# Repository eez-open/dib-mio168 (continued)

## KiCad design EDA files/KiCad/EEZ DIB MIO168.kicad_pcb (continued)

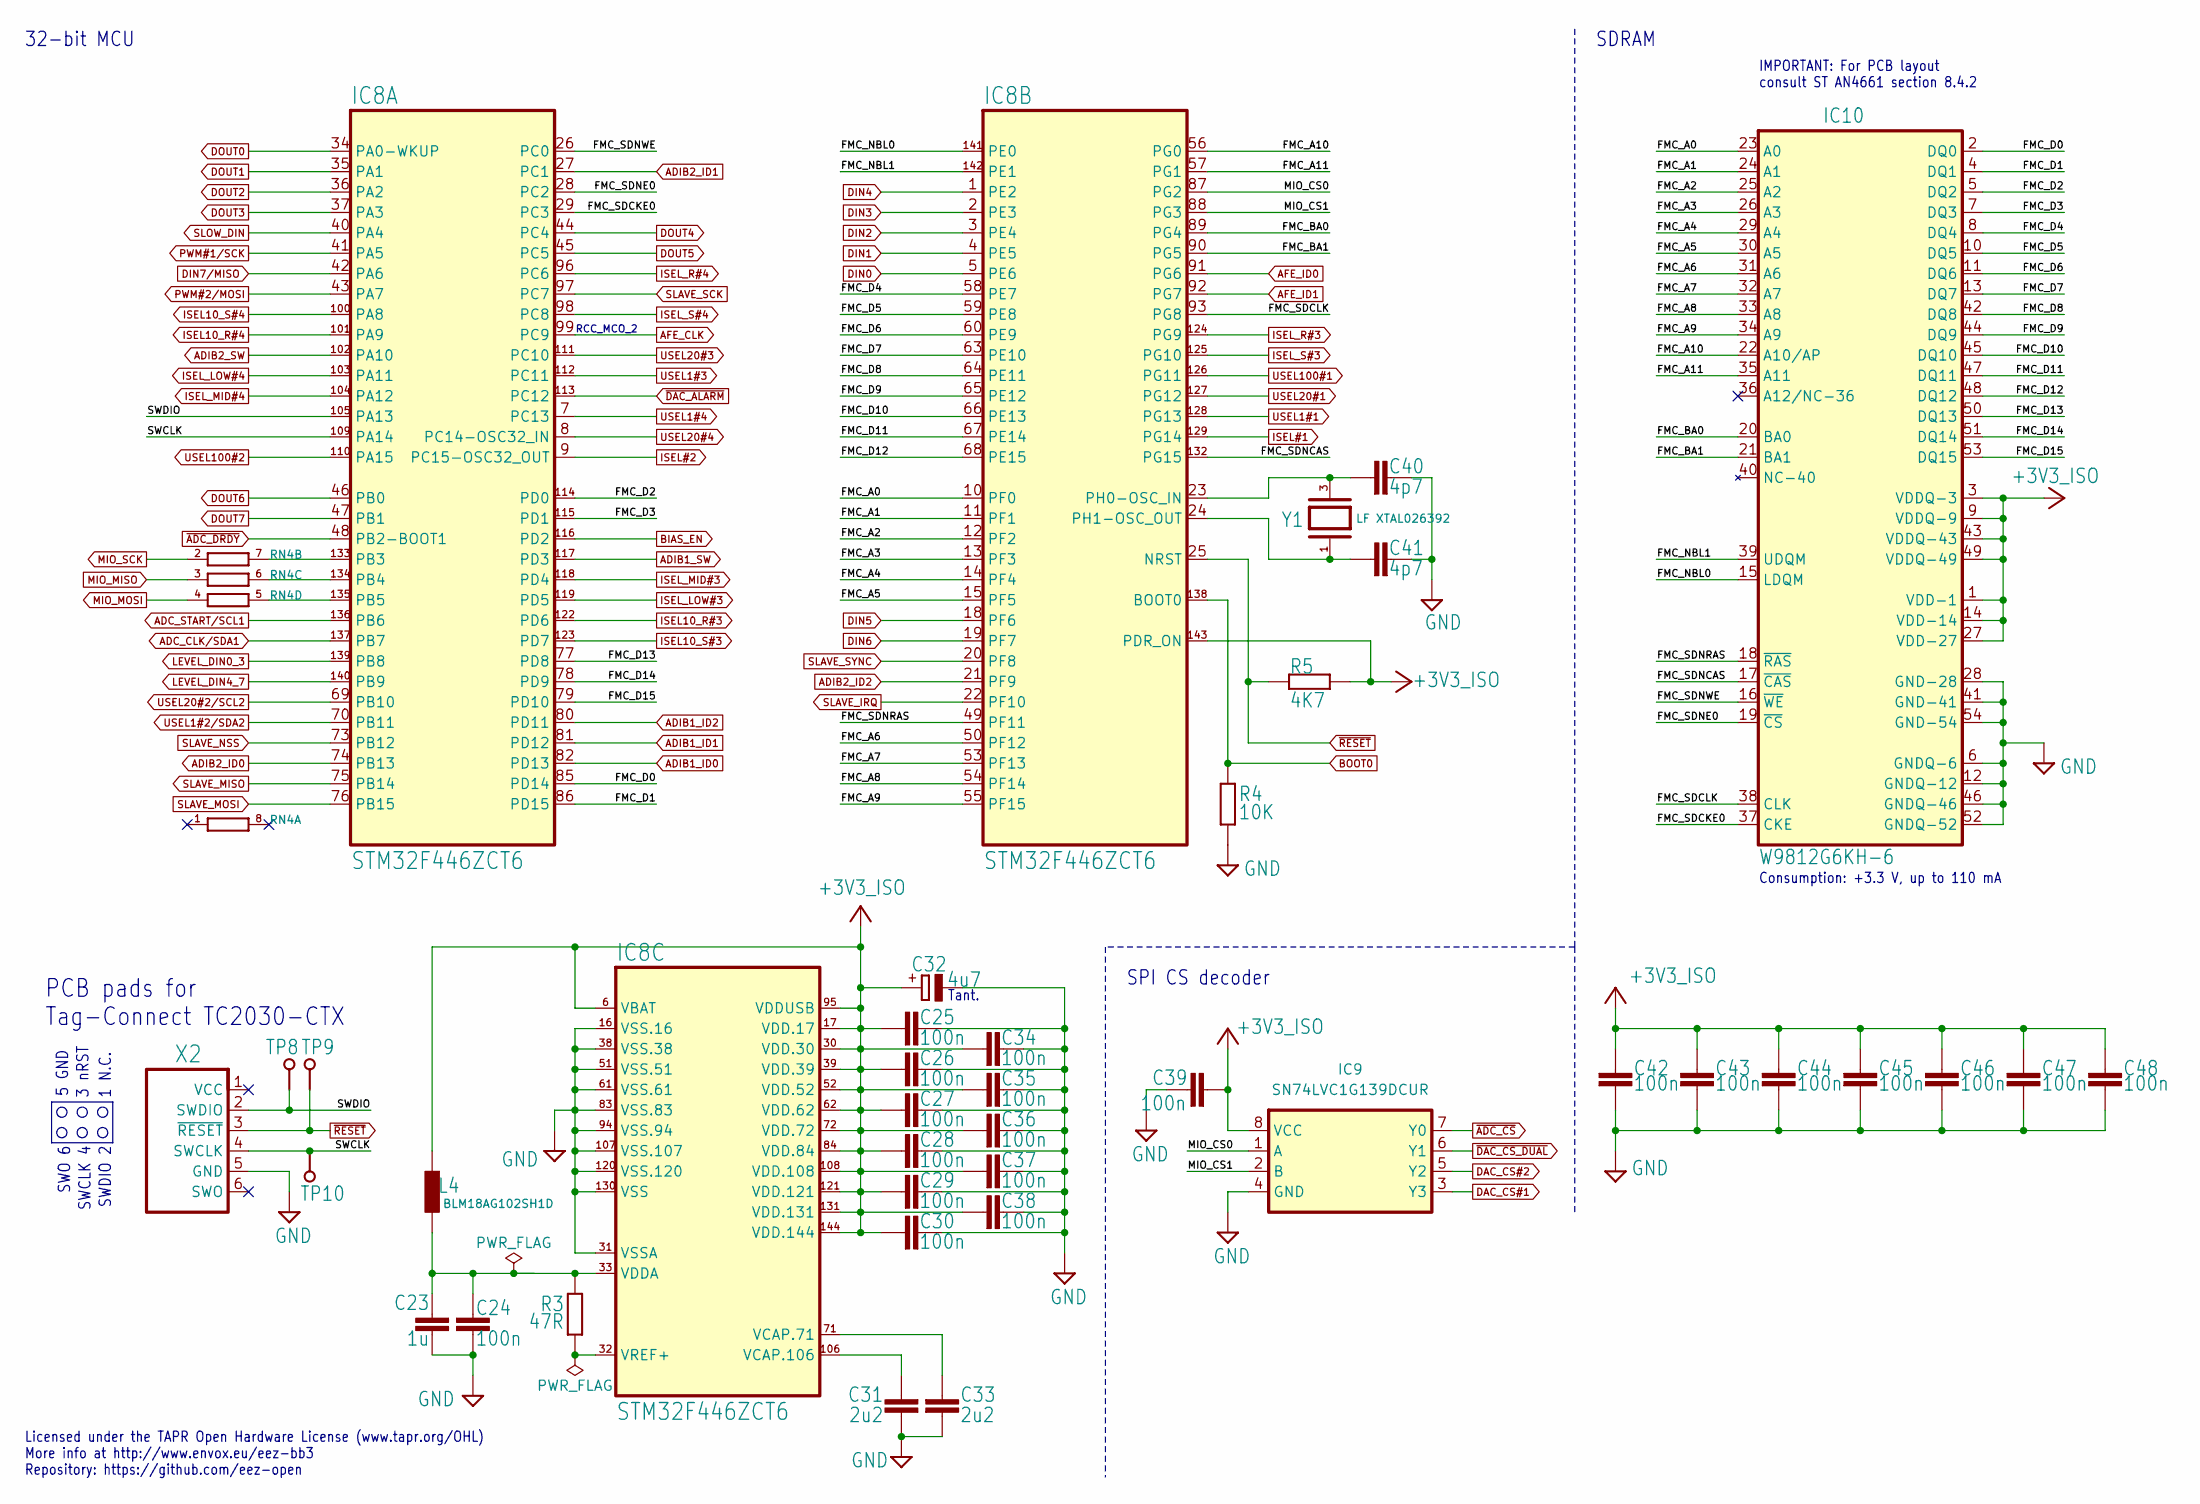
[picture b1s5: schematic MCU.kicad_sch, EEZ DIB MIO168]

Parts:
C23: 1u; C_0805_2012Metric; DigiKey 490-10494-2-ND
C24, C25, C26, C27, C28, C29, C30, C34, C35, C36, C37, C38, C39, C42, C43, C44, C45, C46, C47, C48: 100n; C_0603_1608Metric; DigiKey 1276-1005-2-ND
C31, C33: 2u2; C_0805_2012Metric; DigiKey 1276-2954-1-ND
C32: 4u7; EC1206; DigiKey 399-9717-1-ND
C40, C41: 4p7; C_0603_1608Metric; DigiKey 311-1740-1-ND
IC8: STM32F446ZCT6; LQFP-144_20X20MM; DigiKey 497-17473-ND
IC9: SN74LVC1G139DCUR; DCU8; DigiKey 296-18203-2-ND
IC10: W9812G6KH-6; TSOPII-54; DigiKey W9812G6KH-6-ND
L4: BLM18AG102SH1D; BEAD0603; DigiKey 490-7809-1-ND
R3: 47R; R_0805_2012Metric; DigiKey P47.0CCT-ND
R4: 10K; R_0805_2012Metric; DigiKey CRGH0603F10K
R5: 4K7; R_0805_2012Metric; DigiKey 311-4.70KCRCT-ND
RN4: DR1206-33R-4/8; CAY16; DigiKey CAY16-330J4LFCT-ND
TP8, TP9, TP10: PCB_TEST_TABSHIELD; Testhole 24_50mils
X2: TC2030
Y1: LF XTAL026392; 12SMX(B); DigiKey 1923-1009-ND

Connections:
+3V3_ISO: C25.1, C26.1, C27.1, C28.1, C29.1, C30.1, C32.+, C34.1, C35.1, C36.1, C37.1, C38.1, C39.1, C42.1, C43.1, C44.1, C45.1, C46.1, C47.1, C48.1, IC8.6 (VBAT), IC8.17 (VDD.17), IC8.30 (VDD.30), IC8.39 (VDD.39), IC8.52 (VDD.52), IC8.62 (VDD.62), IC8.72 (VDD.72), IC8.84 (VDD.84), IC8.95 (VDDUSB), IC8.108 (VDD.108), IC8.121 (VDD.121), IC8.131 (VDD.131), IC8.143 (PDR_ON), IC8.144 (VDD.144), IC9.8 (VCC), IC10.1 (VDD-1), IC10.3 (VDDQ-3), IC10.9 (VDDQ-9), IC10.14 (VDD-14), IC10.27 (VDD-27), IC10.43 (VDDQ-43), IC10.49 (VDDQ-49), L4.1, R5.1; also elsewhere on the board
/MCU/FMC_A0: IC8.10 (PF0), IC10.23 (A0)
/MCU/FMC_A1: IC8.11 (PF1), IC10.24 (A1)
/MCU/FMC_A2: IC8.12 (PF2), IC10.25 (A2)
/MCU/FMC_A3: IC8.13 (PF3), IC10.26 (A3)
/MCU/FMC_A4: IC8.14 (PF4), IC10.29 (A4)
/MCU/FMC_A5: IC8.15 (PF5), IC10.30 (A5)
/MCU/FMC_A6: IC8.50 (PF12), IC10.31 (A6)
/MCU/FMC_A7: IC8.53 (PF13), IC10.32 (A7)
/MCU/FMC_A8: IC8.54 (PF14), IC10.33 (A8)
/MCU/FMC_A9: IC8.55 (PF15), IC10.34 (A9)
/MCU/FMC_A10: IC8.56 (PG0), IC10.22 (A10/AP)
/MCU/FMC_A11: IC8.57 (PG1), IC10.35 (A11)
/MCU/FMC_BA0: IC8.89 (PG4), IC10.20 (BA0)
/MCU/FMC_BA1: IC8.90 (PG5), IC10.21 (BA1)
/MCU/FMC_D0: IC8.85 (PD14), IC10.2 (DQ0)
/MCU/FMC_D1: IC8.86 (PD15), IC10.4 (DQ1)
/MCU/FMC_D2: IC8.114 (PD0), IC10.5 (DQ2)
/MCU/FMC_D3: IC8.115 (PD1), IC10.7 (DQ3)
/MCU/FMC_D4: IC8.58 (PE7), IC10.8 (DQ4)
/MCU/FMC_D5: IC8.59 (PE8), IC10.10 (DQ5)
/MCU/FMC_D6: IC8.60 (PE9), IC10.11 (DQ6)
/MCU/FMC_D7: IC8.63 (PE10), IC10.13 (DQ7)
/MCU/FMC_D8: IC8.64 (PE11), IC10.42 (DQ8)
/MCU/FMC_D9: IC8.65 (PE12), IC10.44 (DQ9)
/MCU/FMC_D10: IC8.66 (PE13), IC10.45 (DQ10)
/MCU/FMC_D11: IC8.67 (PE14), IC10.47 (DQ11)
/MCU/FMC_D12: IC8.68 (PE15), IC10.48 (DQ12)
/MCU/FMC_D13: IC8.77 (PD8), IC10.50 (DQ13)
/MCU/FMC_D14: IC8.78 (PD9), IC10.51 (DQ14)
/MCU/FMC_D15: IC8.79 (PD10), IC10.53 (DQ15)
/MCU/FMC_NBL0: IC8.141 (PE0), IC10.15 (LDQM)
/MCU/FMC_NBL1: IC8.142 (PE1), IC10.39 (UDQM)
/MCU/FMC_SDCKE0: IC8.29 (PC3), IC10.37 (CKE)
/MCU/FMC_SDCLK: IC8.93 (PG8), IC10.38 (CLK)
/MCU/FMC_SDNCAS: IC8.132 (PG15), IC10.17 (~CAS)
/MCU/FMC_SDNE0: IC8.28 (PC2), IC10.19 (~CS)
/MCU/FMC_SDNRAS: IC8.49 (PF11), IC10.18 (~RAS)
/MCU/FMC_SDNWE: IC8.26 (PC0), IC10.16 (~WE)
/MCU/MIO_CS0: IC8.87 (PG2), IC9.1 (A)
/MCU/MIO_CS1: IC8.88 (PG3), IC9.2 (B)
/MCU/SWCLK: IC8.109 (PA14), TP10.1, X2.4 (SWCLK)
/MCU/SWDIO: IC8.105 (PA13), TP8.1, X2.2 (SWDIO)
ADC_CLK/SDA1: IC8.137 (PB7); also elsewhere on the board
ADC_START/SCL1: IC8.136 (PB6); also elsewhere on the board
ADIB1_ID0: IC8.82 (PD13); also elsewhere on the board
ADIB1_ID1: IC8.81 (PD12); also elsewhere on the board
ADIB1_ID2: IC8.80 (PD11); also elsewhere on the board
ADIB1_SW: IC8.117 (PD3); also elsewhere on the board
ADIB2_ID0: IC8.74 (PB13); also elsewhere on the board
ADIB2_ID1: IC8.27 (PC1); also elsewhere on the board
ADIB2_ID2: IC8.21 (PF9); also elsewhere on the board
ADIB2_SW: IC8.102 (PA10); also elsewhere on the board
AFE_CLK: IC8.99 (PC9); also elsewhere on the board
AFE_ID0: IC8.91 (PG6); also elsewhere on the board
AFE_ID1: IC8.92 (PG7); also elsewhere on the board
BIAS_EN: IC8.116 (PD2); also elsewhere on the board
BOOT0: IC8.138 (BOOT0), R4.2; also elsewhere on the board
DAC_CS#1: IC9.3 (Y3); also elsewhere on the board
DAC_CS#2: IC9.5 (Y2); also elsewhere on the board
DIN0: IC8.5 (PE6); also elsewhere on the board
DIN1: IC8.4 (PE5); also elsewhere on the board
DIN2: IC8.3 (PE4); also elsewhere on the board
DIN3: IC8.2 (PE3); also elsewhere on the board
DIN4: IC8.1 (PE2); also elsewhere on the board
DIN5: IC8.18 (PF6); also elsewhere on the board
DIN6: IC8.19 (PF7); also elsewhere on the board
DIN7/MISO: IC8.42 (PA6); also elsewhere on the board
DOUT0: IC8.34 (PA0-WKUP); also elsewhere on the board
DOUT1: IC8.35 (PA1); also elsewhere on the board
DOUT2: IC8.36 (PA2); also elsewhere on the board
DOUT3: IC8.37 (PA3); also elsewhere on the board
DOUT4: IC8.44 (PC4); also elsewhere on the board
DOUT5: IC8.45 (PC5); also elsewhere on the board
DOUT6: IC8.46 (PB0); also elsewhere on the board
DOUT7: IC8.47 (PB1); also elsewhere on the board
GND: C23.2, C24.2, C25.2, C26.2, C27.2, C28.2, C29.2, C30.2, C31.1, C32.-, C33.1, C34.2, C35.2, C36.2, C37.2, C38.2, C39.2, C40.1, C41.1, C42.2, C43.2, C44.2, C45.2, C46.2, C47.2, C48.2, IC8.16 (VSS.16), IC8.31 (VSSA), IC8.38 (VSS.38), IC8.51 (VSS.51), IC8.61 (VSS.61), IC8.83 (VSS.83), IC8.94 (VSS.94), IC8.107 (VSS.107), IC8.120 (VSS.120), IC8.130 (VSS), IC9.4 (GND), IC10.6 (GNDQ-6), IC10.12 (GNDQ-12), IC10.28 (GND-28), IC10.41 (GND-41), IC10.46 (GNDQ-46), IC10.52 (GNDQ-52), IC10.54 (GND-54), R4.1, X2.5 (GND); also elsewhere on the board
ISEL10_R#3: IC8.122 (PD6); also elsewhere on the board
ISEL10_R#4: IC8.101 (PA9); also elsewhere on the board
ISEL10_S#3: IC8.123 (PD7); also elsewhere on the board
ISEL10_S#4: IC8.100 (PA8); also elsewhere on the board
ISEL#1: IC8.129 (PG14); also elsewhere on the board
ISEL#2: IC8.9 (PC15-OSC32_OUT); also elsewhere on the board
ISEL_LOW#3: IC8.119 (PD5); also elsewhere on the board
ISEL_LOW#4: IC8.103 (PA11); also elsewhere on the board
ISEL_MID#3: IC8.118 (PD4); also elsewhere on the board
ISEL_MID#4: IC8.104 (PA12); also elsewhere on the board
ISEL_R#3: IC8.124 (PG9); also elsewhere on the board
ISEL_R#4: IC8.96 (PC6); also elsewhere on the board
ISEL_S#3: IC8.125 (PG10); also elsewhere on the board
ISEL_S#4: IC8.98 (PC8); also elsewhere on the board
LEVEL_DIN0_3: IC8.139 (PB8); also elsewhere on the board
LEVEL_DIN4_7: IC8.140 (PB9); also elsewhere on the board
MIO_MISO: RN4.3 (1); also elsewhere on the board
MIO_MOSI: RN4.4 (1); also elsewhere on the board
MIO_SCK: RN4.2 (1); also elsewhere on the board
unnamed: IC8.133 (PB3), RN4.7 (2)
unnamed: IC8.134 (PB4), RN4.6 (2)
unnamed: IC8.135 (PB5), RN4.5 (2)
unnamed: C40.2, IC8.23 (PH0-OSC_IN), Y1.3, Y1.4 (NC)
unnamed: C41.2, IC8.24 (PH1-OSC_OUT), Y1.1, Y1.2 (NC)
unnamed: C33.2, IC8.71 (VCAP.71)
unnamed: C31.2, IC8.106 (VCAP.106)
unnamed: C23.1, C24.1, IC8.33 (VDDA), L4.2, R3.1
unnamed: IC8.32 (VREF+), R3.2
PWM#1/SCK: IC8.41 (PA5); also elsewhere on the board
PWM#2/MOSI: IC8.43 (PA7); also elsewhere on the board
SLAVE_IRQ: IC8.22 (PF10); also elsewhere on the board
SLAVE_MISO: IC8.75 (PB14); also elsewhere on the board
SLAVE_MOSI: IC8.76 (PB15); also elsewhere on the board
SLAVE_NSS: IC8.73 (PB12); also elsewhere on the board
SLAVE_SCK: IC8.97 (PC7); also elsewhere on the board
SLAVE_SYNC: IC8.20 (PF8); also elsewhere on the board
SLOW_DIN: IC8.40 (PA4); also elsewhere on the board
USEL1#1: IC8.128 (PG13); also elsewhere on the board
USEL1#2/SDA2: IC8.70 (PB11); also elsewhere on the board
USEL1#3: IC8.112 (PC11); also elsewhere on the board
USEL1#4: IC8.7 (PC13); also elsewhere on the board
USEL20#1: IC8.127 (PG12); also elsewhere on the board
USEL20#2/SCL2: IC8.69 (PB10); also elsewhere on the board
USEL20#3: IC8.111 (PC10); also elsewhere on the board
USEL20#4: IC8.8 (PC14-OSC32_IN); also elsewhere on the board
USEL100#1: IC8.126 (PG11); also elsewhere on the board
USEL100#2: IC8.110 (PA15); also elsewhere on the board
~ADC_CS: IC9.7 (Y0); also elsewhere on the board
~ADC_DRDY: IC8.48 (PB2-BOOT1); also elsewhere on the board
~DAC_ALARM: IC8.113 (PC12); also elsewhere on the board
~DAC_CS_DUAL: IC9.6 (Y1); also elsewhere on the board
~RESET: IC8.25 (NRST), R5.2, TP9.1, X2.3 (~RESET); also elsewhere on the board

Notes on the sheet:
3 nRST
SWO 6
32-bit MCU
SWCLK 4
SWDIO 2
1 N.C.
Tant.
RCC_MCO_2
5 GND
PCB pads for Tag-Connect TC2030-CTX
Consumption: +3.3 V, up to 110 mA
SPI CS decoder
SDRAM
IMPORTANT: For PCB layout consult ST AN4661 section 8.4.2
Licensed under the TAPR Open Hardware License (www.tapr.org/OHL) More info at http://www.envox.eu/eez-bb3 Repository: https://github.com/eez-open

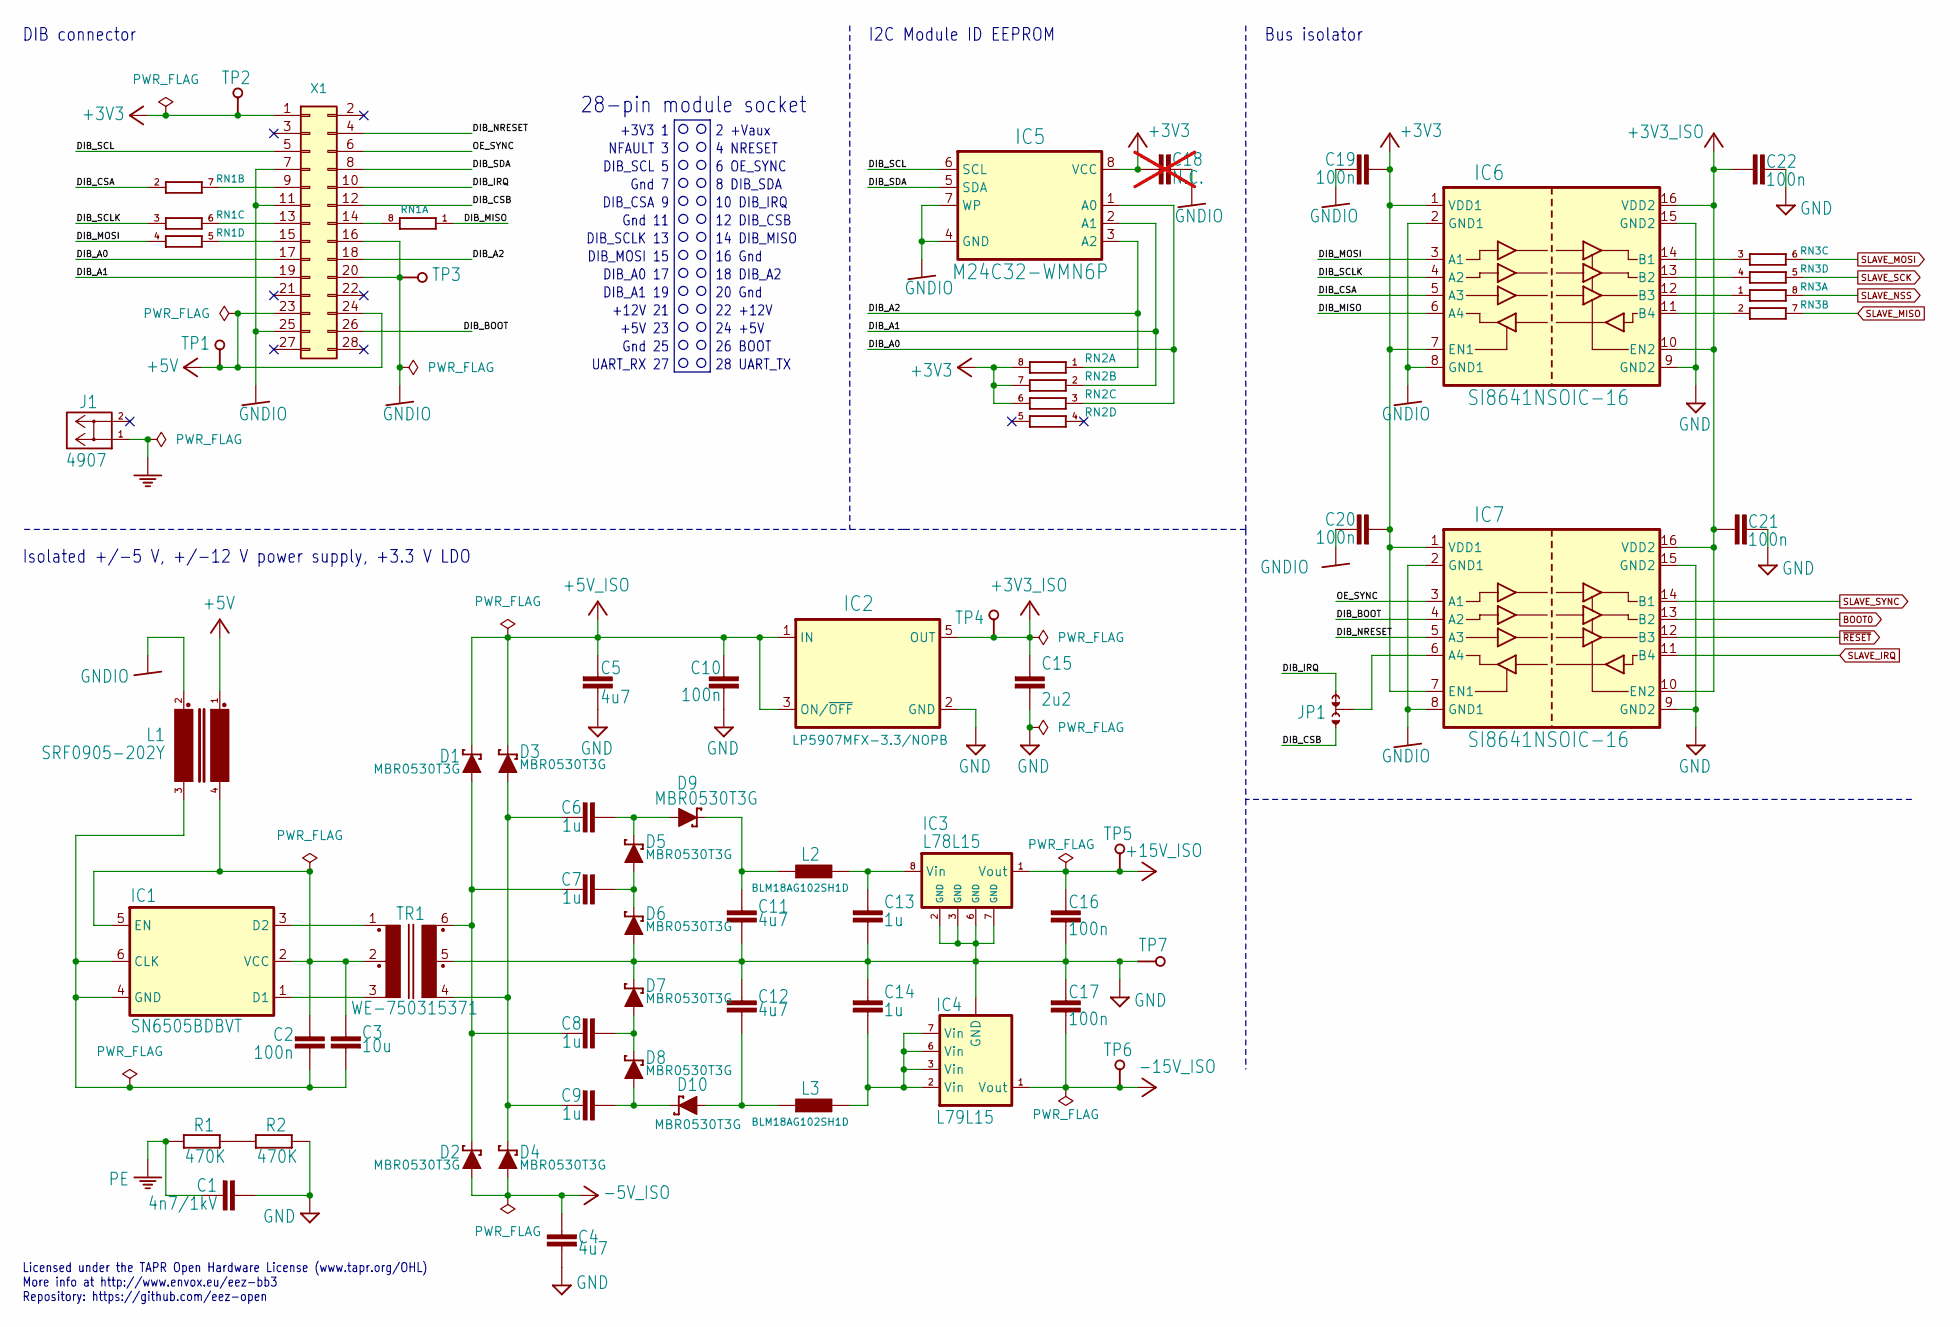
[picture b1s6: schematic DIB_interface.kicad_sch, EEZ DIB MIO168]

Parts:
C1: 4n7/1kV; C_1206_3216Metric; DigiKey 732-12074-2-ND
C2, C10, C16, C17, C19, C20, C21, C22: 100n; C_0603_1608Metric; DigiKey 1276-1005-2-ND
C3: 10u; C_1206_3216Metric; DigiKey 1276-2872-1-ND
C4, C5, C11, C12: 4u7; C_0805_2012Metric; DigiKey 490-14466-1-ND
C6, C7, C8, C9, C13, C14: 1u; C_0805_2012Metric; DigiKey 490-10494-2-ND
C15: 2u2; C_0805_2012Metric; DigiKey 1276-2954-1-ND
C18: N.C.; C_0603_1608Metric; not fitted
D1, D2, D3, D4, D5, D6, D7, D8, D9, D10: MBR0530T3G; SOD123; DigiKey 863-MBR0530T3G
IC1: SN6505BDBVT; DBV0006A_N; DigiKey 296-43154-2-ND
IC2: LP5907MFX-3.3/NOPB; SOT23-5L_STM; DigiKey 296-38557-2-ND
IC3: L78L15; SOIC127P600X173-8N; DigiKey MC78L15ACDR2GOSDKR-ND
IC4: L79L15; SOIC127P600X173-8N; DigiKey MC79L15ABDR2GOSDKR
IC5: M24C32-WMN6P; SOIC127P600X173-8N; DigiKey 497-8572-5-ND
IC6, IC7: SI8641NSOIC-16; SOIC127P600X265-16N; DigiKey 336-2566-ND
J1: 4907; DigiKey 36-4907-ND
JP1: JP3-CUT-0805-ROTATED; JP3 shorted
L1: SRF0905-202Y; SRF0905; DigiKey SRF0905-202YCT-ND
L2, L3: BLM18AG102SH1D; BEAD0603; DigiKey 490-7809-1-ND
R1, R2: 470K; R_0805_2012Metric; DigiKey 13-RT0805FRE07470KLDKR-ND
RN1, RN3: DR1206-33R-4/8; CAY16; DigiKey CAY16-330J4LFCT-ND
RN2: DR1206-47K-4/8; CAY16; DigiKey CAY16-330J4LFCT-ND
TP1, TP2, TP3, TP4, TP5, TP6, TP7: PCB_TEST_TABSHIELD; Testhole 24_50mils
TR1: WE-750315371; MURATA_78615; DigiKey 1297-1178-1-ND
X1: 77317-104-28LF; DigiKey S2111EC-14-ND

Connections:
+3V3: C18.2, C19.1, C20.1, IC5.8 (VCC), IC6.1 (VDD1), IC6.7 (EN1), IC7.1 (VDD1), IC7.7 (EN1), RN2.6 (2), RN2.7 (2), RN2.8 (2), TP2.1, X1.1
+3V3_ISO: C15.1, C21.2, C22.2, IC2.5 (OUT), IC6.10 (EN2), IC6.16 (VDD2), IC7.10 (EN2), IC7.16 (VDD2), TP4.1; also elsewhere on the board
+5V: L1.1, TP1.1, X1.23, X1.24
+5V_ISO: C5.2, C10.1, D1.C, D3.C, IC2.1 (IN), IC2.3 (ON/~OFF); also elsewhere on the board
+15V_ISO: C16.1, IC3.1 (Vout), TP5.1; also elsewhere on the board
-5V_ISO: C4.2, D2.A, D4.A; also elsewhere on the board
-15V_ISO: C17.2, IC4.1 (Vout), TP6.1; also elsewhere on the board
/DIB interface/DIB_A0: IC5.1 (A0), RN2.3 (1), X1.17
/DIB interface/DIB_A1: IC5.2 (A1), RN2.2 (1), X1.19
/DIB interface/DIB_A2: IC5.3 (A2), RN2.1, X1.18
/DIB interface/DIB_BOOT: IC7.4 (A2), X1.26
/DIB interface/DIB_CSA: IC6.5 (A3), RN1.2 (1)
/DIB interface/DIB_CSB: JP1.NO, X1.12
/DIB interface/DIB_IRQ: JP1.NC, X1.10
/DIB interface/DIB_MISO: IC6.6 (A4), RN1.1
/DIB interface/DIB_MOSI: IC6.3 (A1), RN1.4 (1)
/DIB interface/DIB_NRESET: IC7.5 (A3), X1.4
/DIB interface/DIB_SCL: IC5.6 (SCL), X1.5
/DIB interface/DIB_SCLK: IC6.4 (A2), RN1.3 (1)
/DIB interface/DIB_SDA: IC5.5 (SDA), X1.8
/DIB interface/OE_SYNC: IC7.3 (A1), X1.6
BOOT0: IC7.13 (B2); also elsewhere on the board
GND: C1.2, C4.1, C5.1, C10.2, C11.2, C12.1, C13.1, C14.2, C15.2, C16.2, C17.1, C21.1, C22.1, D6.A, D7.C, IC2.2 (GND), IC3.2 (GND), IC3.3 (GND), IC3.6 (GND), IC3.7 (GND), IC4.5 (GND), IC6.9 (GND2), IC6.15 (GND2), IC7.9 (GND2), IC7.15 (GND2), R2.2, TP7.1, TR1.5; also elsewhere on the board
GNDIO: C18.1, C19.2, C20.2, IC5.4 (GND), IC5.7 (WP), IC6.2 (GND1), IC6.8 (GND1), IC7.2 (GND1), IC7.8 (GND1), L1.2, TP3.1, X1.7, X1.11, X1.16, X1.20, X1.25
unnamed: C6.1, D5.C, D9.A
unnamed: C6.2, C9.2, D3.A, D4.C, TR1.4
unnamed: C7.1, D5.A, D6.C
unnamed: C7.2, C8.2, D1.A, D2.C, TR1.6
unnamed: C8.1, D7.A, D8.C
unnamed: C9.1, D8.A, D10.C
unnamed: C11.1, D9.C, L2.1
unnamed: C12.2, D10.A, L3.1
unnamed: C14.1, IC4.2 (Vin), IC4.3 (Vin), IC4.6 (Vin), IC4.7 (Vin), L3.2
unnamed: C2.2, C3.1, IC1.4 (GND), IC1.6 (CLK), L1.3
unnamed: IC1.1 (D1), TR1.3
unnamed: IC1.3 (D2), TR1.1
unnamed: C2.1, C3.2, IC1.2 (VCC), IC1.5 (EN), L1.4, TR1.2
unnamed: C13.2, IC3.8 (Vin), L2.2
unnamed: IC6.14 (B1), RN3.3 (1)
unnamed: IC6.13 (B2), RN3.4 (1)
unnamed: IC6.12 (B3), RN3.1
unnamed: IC6.11 (B4), RN3.2 (1)
unnamed: IC7.6 (A4), JP1.COM
unnamed: R1.2, R2.1
unnamed: RN1.8 (2), X1.14
unnamed: RN1.7 (2), X1.9
unnamed: RN1.6 (2), X1.13
unnamed: RN1.5 (2), X1.15
PE: C1.1, J1.1, R1.1
SLAVE_IRQ: IC7.11 (B4); also elsewhere on the board
SLAVE_MISO: RN3.7 (2); also elsewhere on the board
SLAVE_MOSI: RN3.6 (2); also elsewhere on the board
SLAVE_NSS: RN3.8 (2); also elsewhere on the board
SLAVE_SCK: RN3.5 (2); also elsewhere on the board
SLAVE_SYNC: IC7.14 (B1); also elsewhere on the board
~RESET: IC7.12 (B3); also elsewhere on the board

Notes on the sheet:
24 +5V
18 DIB_A2
28 UART_TX
DIB_A0 17
16 Gnd
DIB_A1 19
6 OE_SYNC
Licensed under the TAPR Open Hardware License (www.tapr.org/OHL) More info at http://www.envox.eu/eez-bb3 Repository: https://github.com/eez-open
Isolated +/-5 V, +/-12 V power supply, +3.3 V LDO
20 Gnd
DIB_SCLK 13
12 DIB_CSB
2 +Vaux
+5V 23
UART_RX 27
22 +12V
DIB connector
8 DIB_SDA
10 DIB_IRQ
DIB_MOSI 15
Gnd 25
DIB_CSA 9
NFAULT 3
I2C Module ID EEPROM
4 NRESET
Gnd 7
DIB_SCL 5
14 DIB_MISO
+3V3 1
Gnd 11
26 BOOT
+12V 21
Bus isolator
28-pin module socket

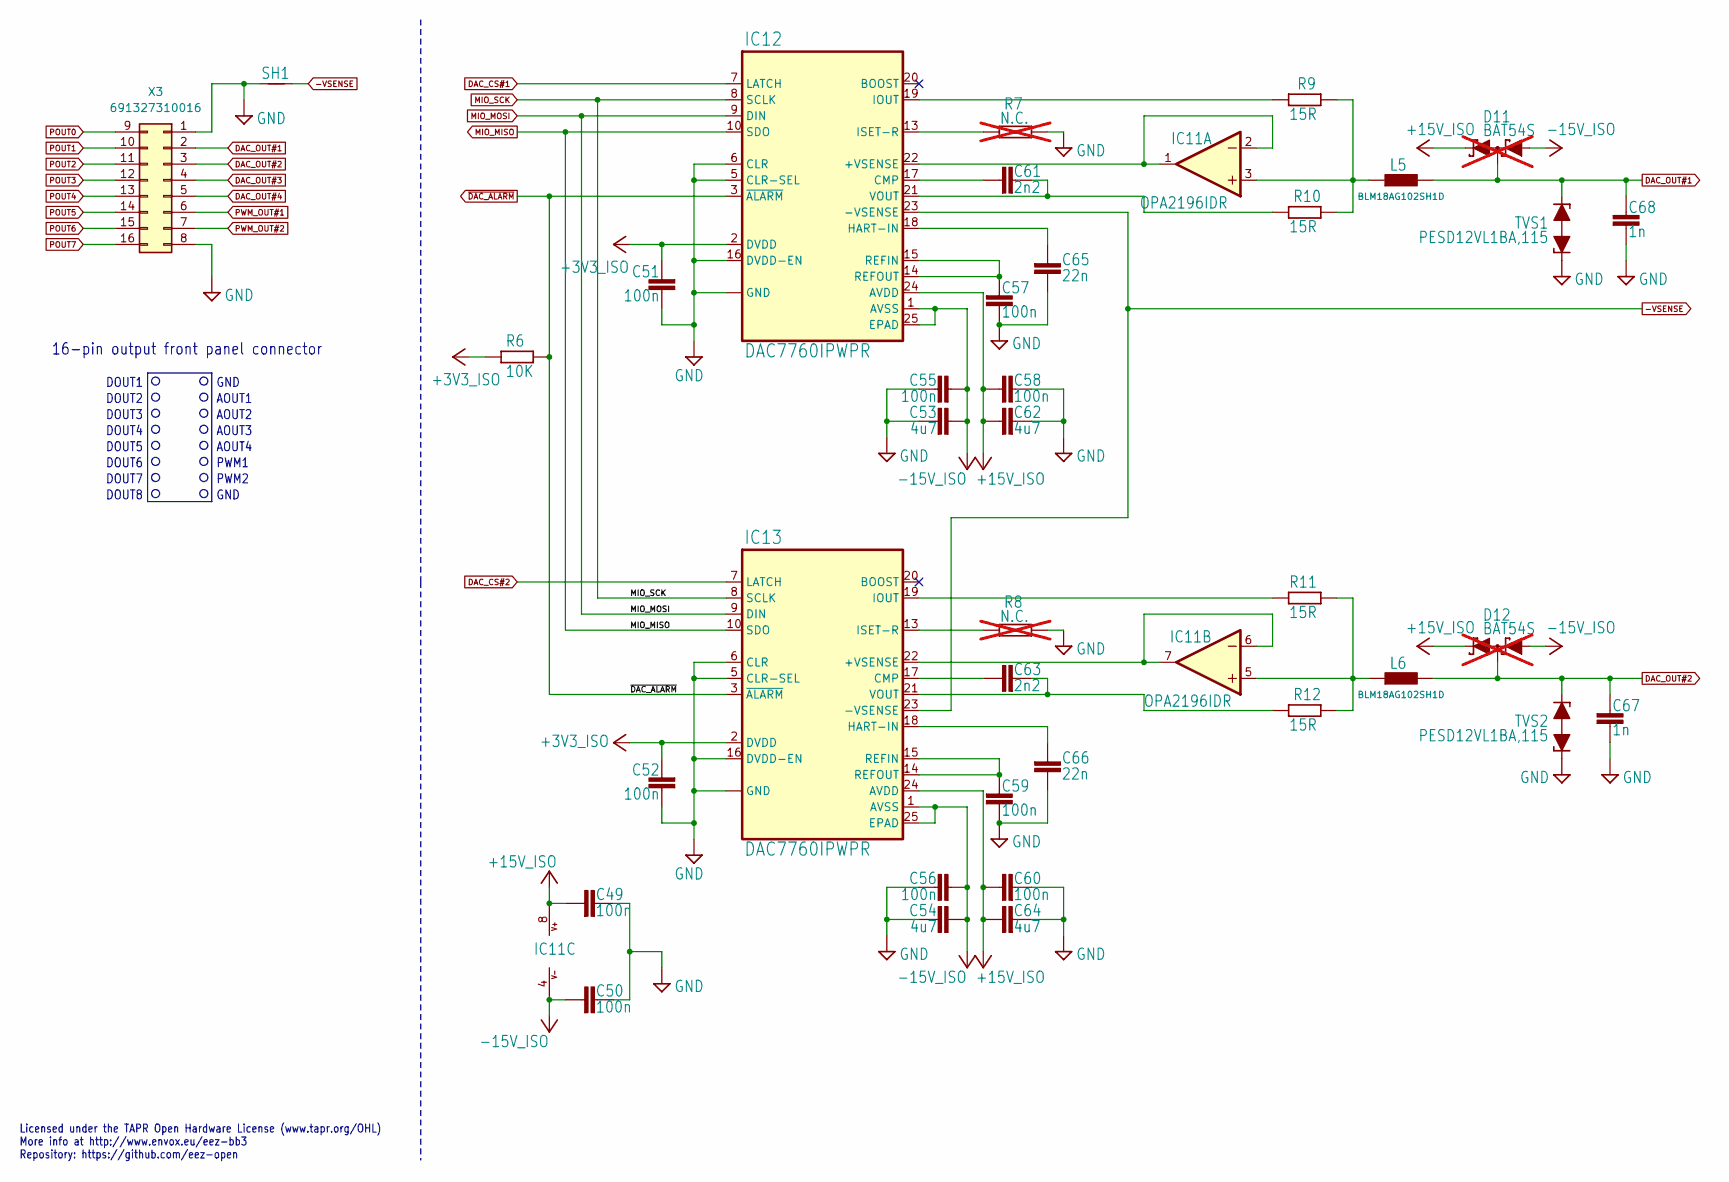
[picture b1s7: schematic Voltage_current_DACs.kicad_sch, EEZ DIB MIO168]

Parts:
C49, C50, C51, C52, C55, C56, C57, C58, C59, C60: 100n; C_0603_1608Metric; DigiKey 1276-1005-2-ND
C53, C54, C62, C64: 4u7; C_0805_2012Metric; DigiKey 490-14466-1-ND
C61, C63: 2n2; C_0805_2012Metric; DigiKey 732-7840-1-ND
C65, C66: 22n; C_0805_2012Metric; DigiKey 399-1163-1-ND
C67, C68: 1n; C_0805_2012Metric; DigiKey 732-7858-1-ND
D11, D12: BAT54S; SOT23-3; DigiKey 497-2522-1-ND; not fitted
IC11: OPA2196IDR; SOIC127P600X173-8N; DigiKey 296-1282-1-ND
IC12, IC13: DAC7760IPWPR; PWP24; DigiKey 296-37188-1-ND
L5, L6: BLM18AG102SH1D; BEAD0603; DigiKey 490-7809-1-ND
R6: 10K; R_0805_2012Metric; DigiKey CRGH0603F10K
R7, R8: N.C.; R_0805_2012Metric; not fitted
R9, R10, R11, R12: 15R; R_0805_2012Metric; DigiKey RNCP0805FTD15R0CT-ND
SH1: SHORTNOHOLE; NetTie-2_SMD_Pad0.5mm
TVS1, TVS2: PESD12VL1BA,115; SOD-323_PESD; DigiKey 1727-3808-1-ND
X3: 691327310016; DigiKey 732-691327310016-ND

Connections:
+3V3_ISO: C51.1, C52.1, IC12.2 (DVDD), IC13.2 (DVDD), R6.1; also elsewhere on the board
+15V_ISO: C49.1, C58.1, C60.1, C62.2, C64.2, D11.2 (C2), D12.2 (C2), IC11.8 (V+), IC12.24 (AVDD), IC13.24 (AVDD); also elsewhere on the board
-15V_ISO: C50.1, C53.2, C54.2, C55.1, C56.1, D11.1 (A1), D12.1 (A1), IC11.4 (V-), IC12.1 (AVSS), IC12.25 (EPAD), IC13.1 (AVSS), IC13.25 (EPAD); also elsewhere on the board
-VSENSE: IC12.23 (-VSENSE), IC13.23 (-VSENSE), SH1.2; also elsewhere on the board
DAC_CS#1: IC12.7 (LATCH); also elsewhere on the board
DAC_CS#2: IC13.7 (LATCH); also elsewhere on the board
DAC_OUT#1: C68.1, D11.3 (C1A2), L5.2, TVS1.C2 (2), X3.2; also elsewhere on the board
DAC_OUT#2: C67.1, D12.3 (C1A2), L6.2, TVS2.C2 (2), X3.3; also elsewhere on the board
DAC_OUT#3: X3.4; also elsewhere on the board
DAC_OUT#4: X3.5; also elsewhere on the board
GND: C49.2, C50.2, C51.2, C52.2, C53.1, C54.1, C55.2, C56.2, C57.2, C58.2, C59.2, C60.2, C62.1, C64.1, C65.1, C66.1, C67.2, C68.2, IC12.4 (GND), IC12.5 (CLR-SEL), IC12.6 (CLR), IC12.11 (GND), IC12.12 (GND), IC12.16 (DVDD-EN), IC13.4 (GND), IC13.5 (CLR-SEL), IC13.6 (CLR), IC13.11 (GND), IC13.12 (GND), IC13.16 (DVDD-EN), R7.1, R8.1, SH1.1, TVS1.C1 (1), TVS2.C1 (1), X3.1, X3.8; also elsewhere on the board
MIO_MISO: IC12.10 (SDO), IC13.10 (SDO); also elsewhere on the board
MIO_MOSI: IC12.9 (DIN), IC13.9 (DIN); also elsewhere on the board
MIO_SCK: IC12.8 (SCLK), IC13.8 (SCLK); also elsewhere on the board
unnamed: IC11.3 (+IN), L5.1, R9.1, R10.1
unnamed: IC11.1 (OUT), IC11.2 (-IN), IC12.22 (+VSENSE)
unnamed: IC11.5 (+IN), L6.1, R11.1, R12.1
unnamed: IC11.6 (-IN), IC11.7 (OUT), IC13.22 (+VSENSE)
unnamed: C61.2, IC12.17 (CMP)
unnamed: C65.2, IC12.18 (HART-IN)
unnamed: IC12.19 (IOUT), R9.2
unnamed: IC12.13 (ISET-R), R7.2
unnamed: C57.1, IC12.14 (REFOUT), IC12.15 (REFIN)
unnamed: C61.1, IC12.21 (VOUT), R10.2
unnamed: C63.2, IC13.17 (CMP)
unnamed: C66.2, IC13.18 (HART-IN)
unnamed: IC13.19 (IOUT), R11.2
unnamed: IC13.13 (ISET-R), R8.2
unnamed: C59.1, IC13.14 (REFOUT), IC13.15 (REFIN)
unnamed: C63.1, IC13.21 (VOUT), R12.2
POUT0: X3.9; also elsewhere on the board
POUT1: X3.10; also elsewhere on the board
POUT2: X3.11; also elsewhere on the board
POUT3: X3.12; also elsewhere on the board
POUT4: X3.13; also elsewhere on the board
POUT5: X3.14; also elsewhere on the board
POUT6: X3.15; also elsewhere on the board
POUT7: X3.16; also elsewhere on the board
PWM_OUT#1: X3.6; also elsewhere on the board
PWM_OUT#2: X3.7; also elsewhere on the board
~DAC_ALARM: IC12.3 (~ALARM), IC13.3 (~ALARM), R6.2; also elsewhere on the board

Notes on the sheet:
AOUT2
16-pin output front panel connector
AOUT1
DOUT7
PWM1
GND
PWM2
DOUT3
Licensed under the TAPR Open Hardware License (www.tapr.org/OHL) More info at http://www.envox.eu/eez-bb3 Repository: https://github.com/eez-open
DOUT6
DOUT8
DOUT4
AOUT3
AOUT4
DOUT2
DOUT5
DOUT1

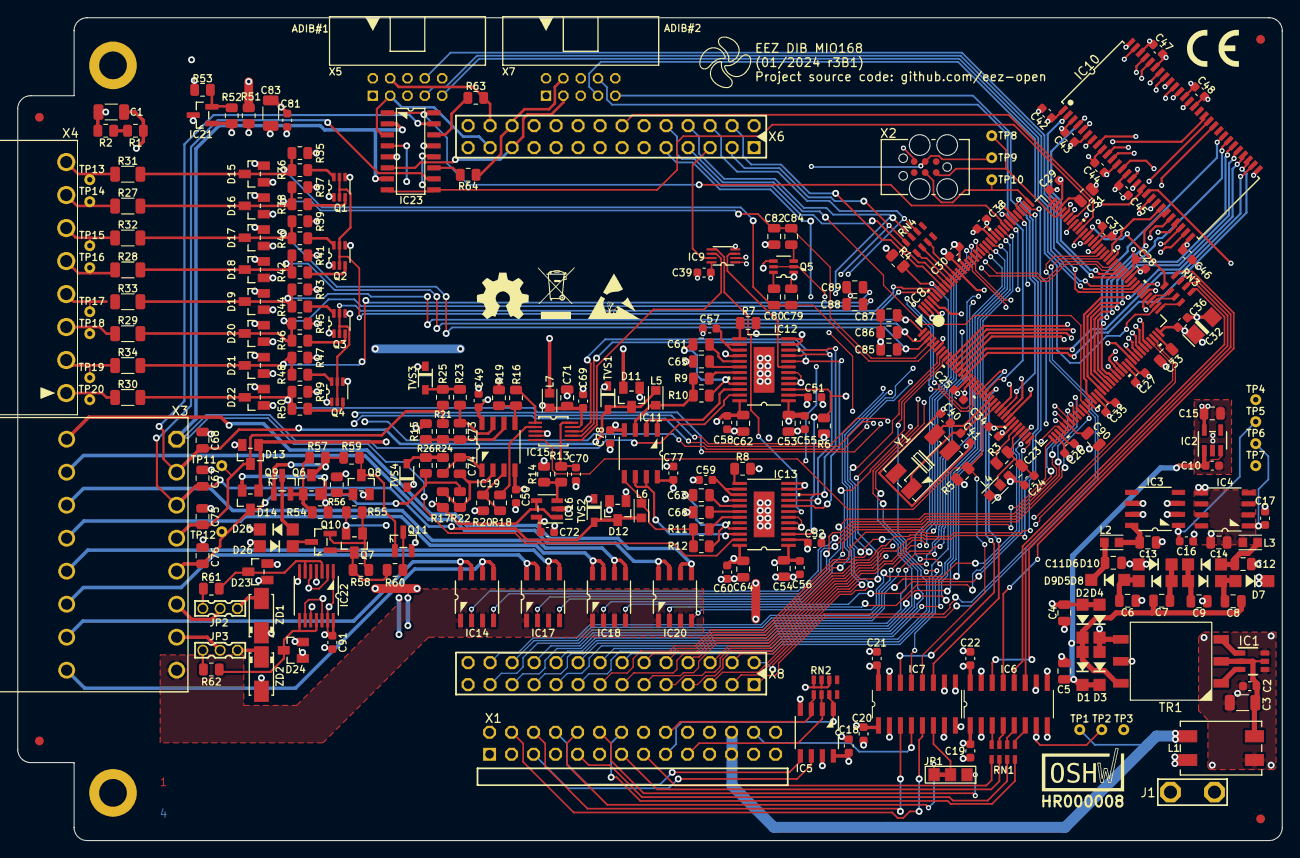
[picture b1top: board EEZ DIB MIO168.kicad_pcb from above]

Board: 4 copper layers, 146.0 x 95.0 mm, 279 parts (0 on the bottom side), 261 nets.

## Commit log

2020-03-09 IC36 name, value added
2020-03-10 BOM added
2020-03-10 readme.md update
2020-03-10 PWM outputs clamp fix
2020-03-10 Vref selection for NTC bias (JP3)
2020-03-13 schematics PDF update
2020-03-14 Changes suggested by @jbb
2020-03-15 2N7002PS package fixed
2020-03-15 PCB preview update
2020-03-19 front panel connectors position adjusted
2020-04-06 #1 fixed
2020-05-05 Slave SPI moved to SPI4
2020-05-18 prototype picture
2020-06-12 IRQ selection jumper
2020-07-08 r1B2 picture update
2020-08-27 Connectors for piggyback, GND and PWM outputs jumpers
2020-09-09 MCU Vdd update
2020-10-11 #4, BOM update
2020-10-17 ZD1, ZD2 added
2020-10-31 PWM outputs pin rearrangement
2020-10-31 swap DOUT0 and DOUT1
2021-01-22 r2B4 version
2021-01-31 PCB ID added
2021-02-07 BOM update
2021-03-29 r2B5, ADIB switcing
2021-03-29 r2B5 .ioc
2021-03-29 BOM, .ioc update
2021-06-04 DIN3 PCB correction
2021-10-08 OSHWA UID
2024-01-19 #6, #7, r1B3 (KiCad)
2024-01-20 PCB preview correction
